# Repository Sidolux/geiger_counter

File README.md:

# geiger_counter
Geiger Counter (STS-5) designed with KiCad

PCB_SCH - KiCad project

source - uC firmware (in future)

Some changes

GPG

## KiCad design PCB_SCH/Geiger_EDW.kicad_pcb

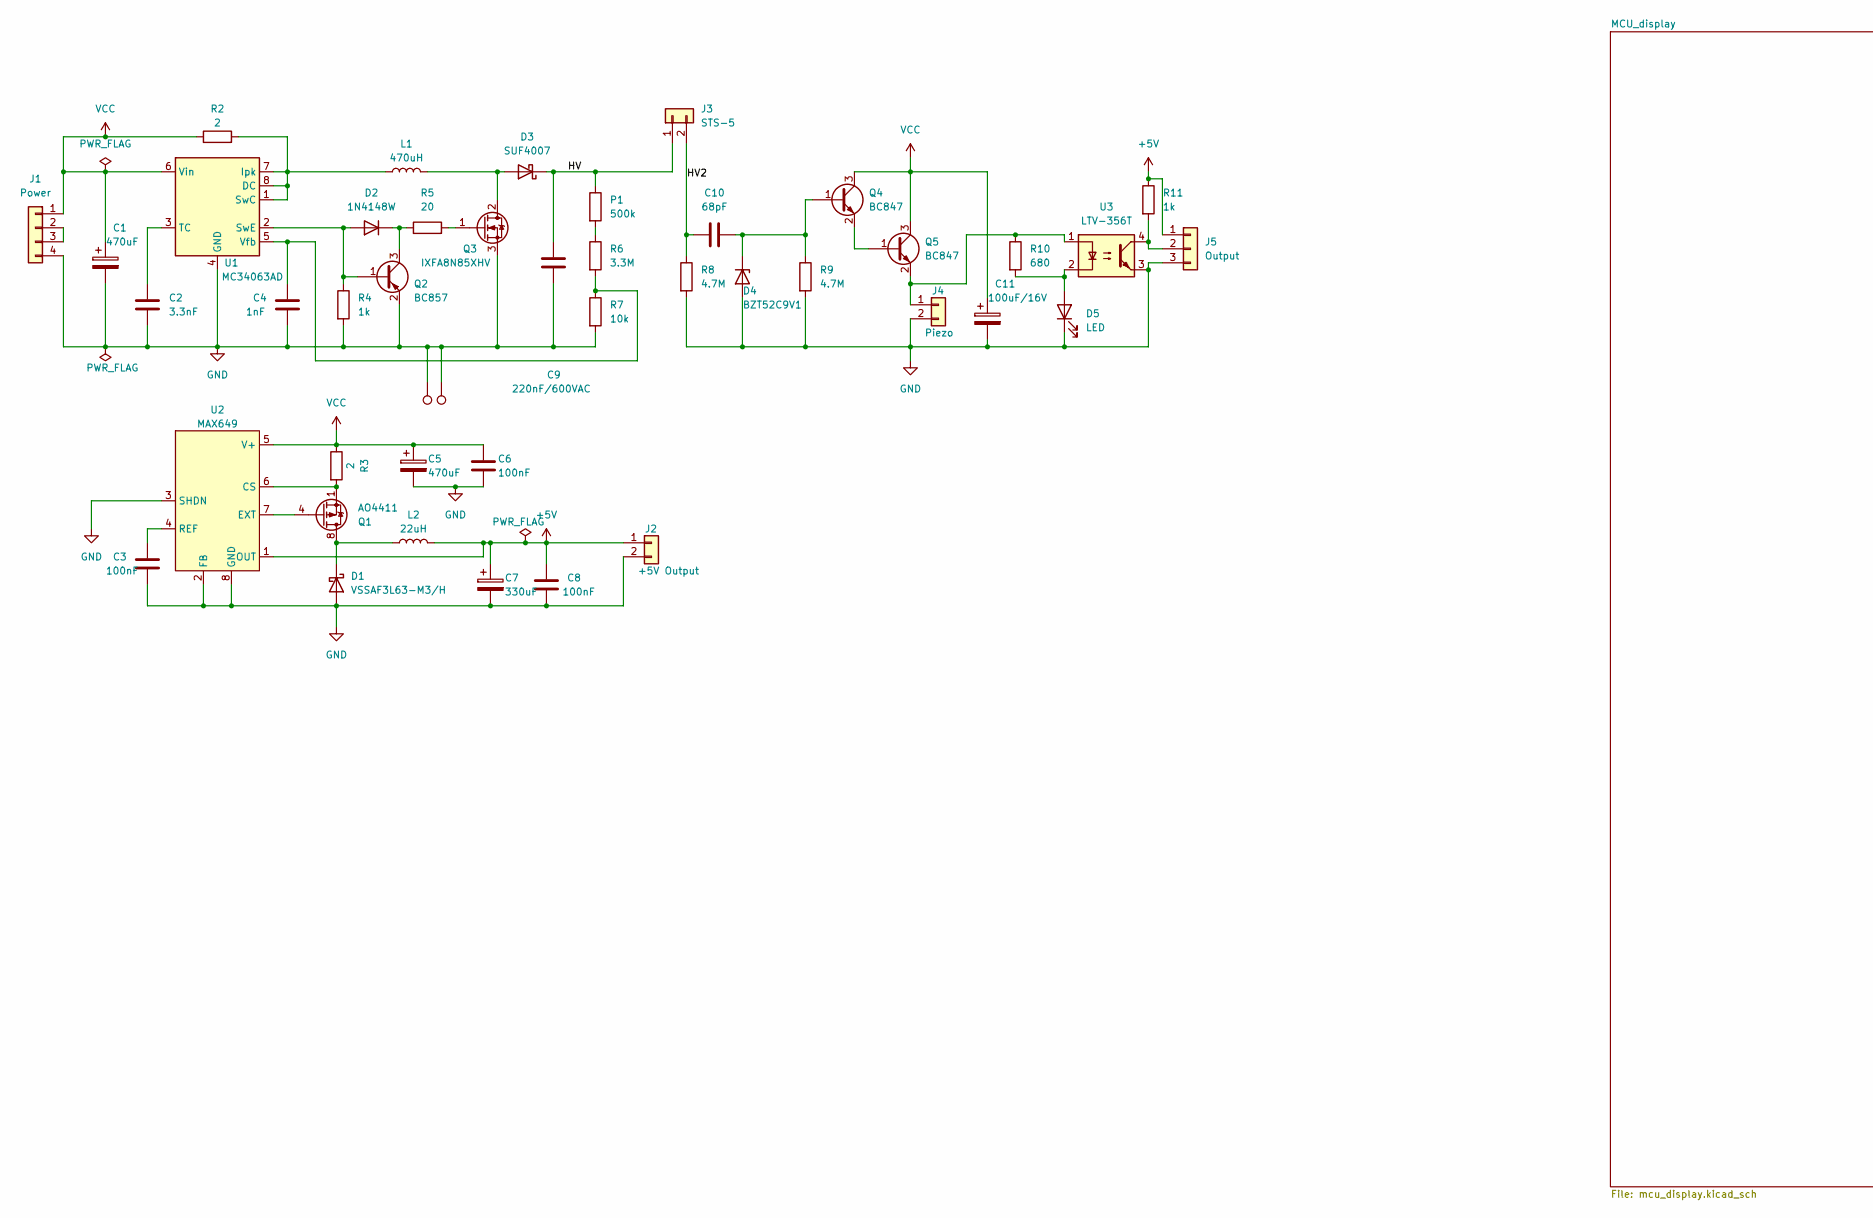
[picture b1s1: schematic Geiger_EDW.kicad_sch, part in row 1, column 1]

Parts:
C1, C5: 470uF; CP_Elec_8x10.5
C2: 3.3nF; C_1206_3216Metric_Pad1.33x1.80mm_HandSolder
C3, C6, C8: 100nF; C_1206_3216Metric_Pad1.33x1.80mm_HandSolder
C4: 1nF; C_1206_3216Metric_Pad1.33x1.80mm_HandSolder
C7: 330uF; CP_Elec_8x10.5
C9: 220nF/600VAC; C_Rect_L41.5mm_W19.0mm_P37.50mm_MKS4
C10: 68pF; C_1206_3216Metric_Pad1.33x1.80mm_HandSolder
C11: 100uF/16V; CP_Elec_8x10.5
D1: VSSAF3L63-M3/H; D_MELF
D2: 1N4148W; D_SOD-123
D3: SUF4007; D_MELF
D4: BZT52C9V1; D_SOD-123
D5: LED; LED_1206_3216Metric_Pad1.42x1.75mm_HandSolder
J1: Power; PinHeader_1x04_P2.54mm_Vertical
J2: +5V Output; PinHeader_1x02_P2.54mm_Vertical
J3: STS-5
J4: Piezo; PinHeader_1x02_P2.54mm_Vertical
J5: Output; PinHeader_1x03_P2.54mm_Vertical
L1: 470uH; L_10.4x10.4_H4.8
L2: 22uH; L_12x12mm_H6mm
P1: 500k; R_1206_3216Metric_Pad1.30x1.75mm_HandSolder
Q1: AO4411; SOIC-8_3.9x4.9mm_P1.27mm
Q2: BC857; SOT-23
Q3: IXFA8N85XHV; TO-263-2
Q4, Q5: BC847; SOT-23
R2, R3: 2; R_1206_3216Metric_Pad1.30x1.75mm_HandSolder
R4, R11: 1k; R_1206_3216Metric_Pad1.30x1.75mm_HandSolder
R5: 20; R_1206_3216Metric_Pad1.30x1.75mm_HandSolder
R6: 3.3M; R_1206_3216Metric_Pad1.30x1.75mm_HandSolder
R7: 10k; R_1206_3216Metric_Pad1.30x1.75mm_HandSolder
R8, R9: 4.7M; R_1206_3216Metric_Pad1.30x1.75mm_HandSolder
R10: 680; R_1206_3216Metric_Pad1.30x1.75mm_HandSolder
TP1, TP2: TestPoint; TestPoint_Loop_D2.60mm_Drill1.4mm_Beaded
U1: MC34063AD; SOIC-8_3.9x4.9mm_P1.27mm
U2: MAX649; SO-8_3.9x4.9mm_P1.27mm
U3: LTV-356T; SO-4_4.4x3.6mm_P2.54mm

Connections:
+5V: C7.1, C8.2, J2.1, J5.1, L2.2, R11.1, U2.1 (OUT); also elsewhere on the board
/HV: C9.1, D3.1 (K), J3.1, P1.1
/HV2: C10.2, J3.2, R8.1
GND: C1.2, C2.2, C3.2, C4.2, C5.2, C6.2, C7.2, C8.1, C9.2, C11.2, D1.2 (A), D4.2 (A), D5.1 (K), J1.4, J2.2, J4.2, J5.3, Q2.2 (E), Q3.3 (S), R4.2, R7.2, R8.2, R9.2, TP1.1, TP2.1, U1.4 (GND), U2.2 (FB), U2.3 (SHDN), U2.8 (GND), U3.3; also elsewhere on the board
unnamed: D1.1 (K), L2.1, Q1.5 (D), Q1.6 (D), Q1.7 (D), Q1.8 (D)
unnamed: D2.2 (A), Q2.1 (B), R4.1, U1.2 (SwE)
unnamed: D2.1 (K), Q2.3 (C), R5.1
unnamed: D3.2 (A), L1.2, Q3.2 (D)
unnamed: C10.1, D4.1 (K), Q4.1 (B), R9.1
unnamed: D5.2 (A), R10.2, U3.2
unnamed: J1.2, J1.3
unnamed: J4.1, Q5.2 (E), R10.1, U3.1
unnamed: J5.2, R11.2, U3.4
unnamed: P1.2, R6.1
unnamed: Q1.4 (G), U2.7 (EXT)
unnamed: Q3.1 (G), R5.2
unnamed: Q4.2 (E), Q5.1 (B)
unnamed: L1.1, R2.2, U1.1 (SwC), U1.7 (Ipk), U1.8 (DC)
unnamed: C2.1, U1.3 (TC)
unnamed: C4.1, R6.2, R7.1, U1.5 (Vfb)
unnamed: Q1.1 (S), Q1.2 (S), Q1.3 (S), R3.2, U2.6 (CS)
unnamed: C3.1, U2.4 (REF)
VCC: C1.1, C5.1, C6.1, C11.1, J1.1, Q4.3 (C), Q5.3 (C), R2.1, R3.1, U1.6 (Vin), U2.5 (V+)

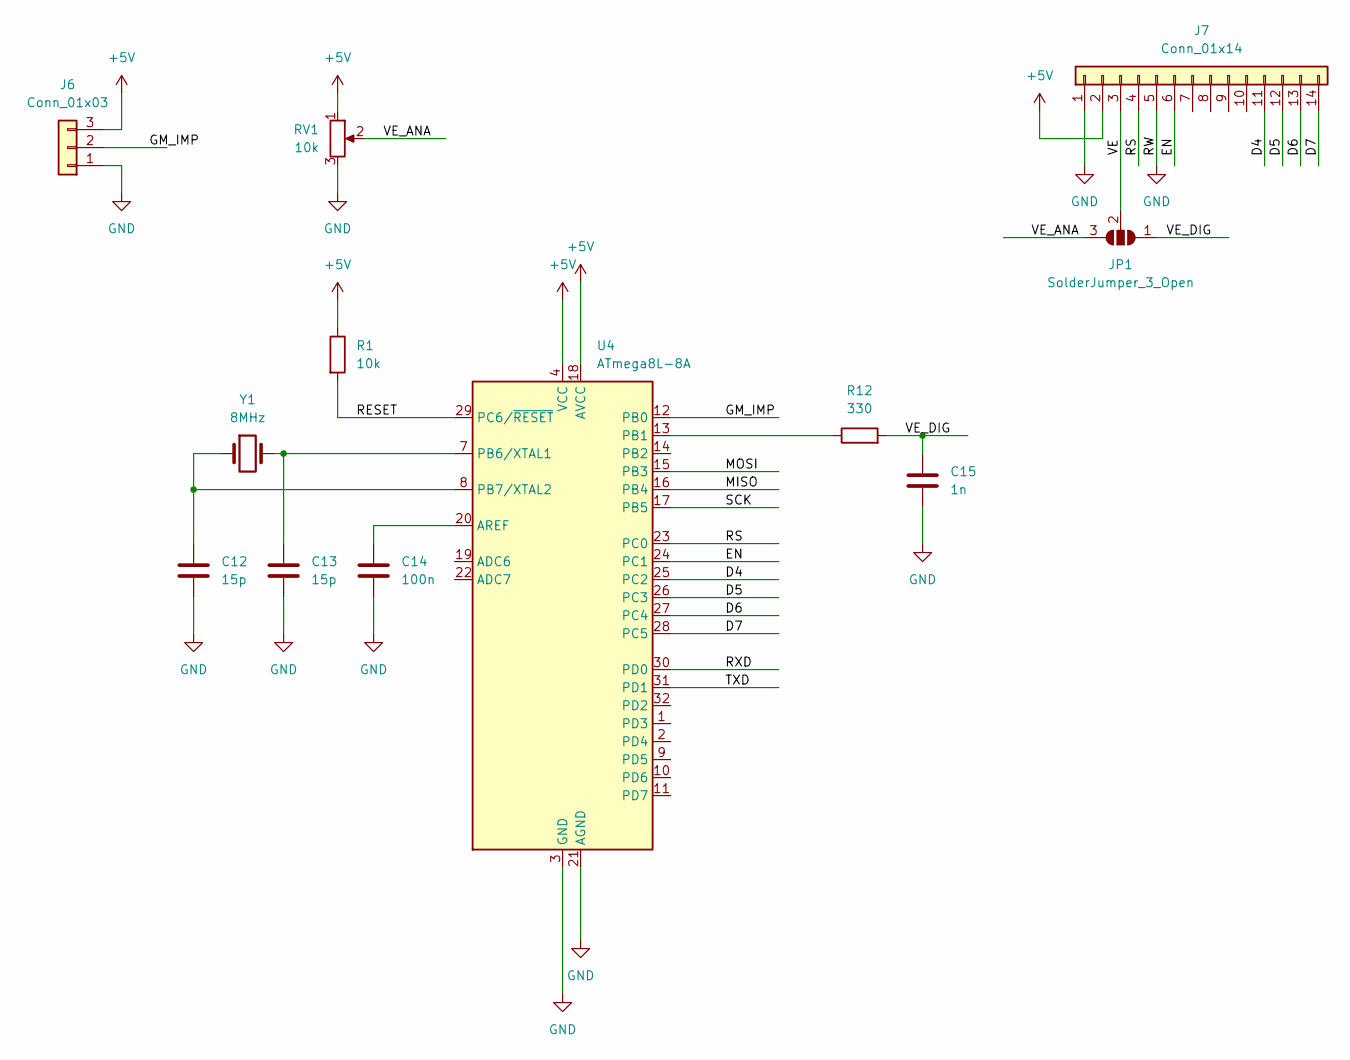
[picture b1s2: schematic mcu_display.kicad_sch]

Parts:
C12, C13: 15p; C_Disc_D3.0mm_W1.6mm_P2.50mm
C14: 100n; C_Disc_D3.8mm_W2.6mm_P2.50mm
C15: 1n; C_Disc_D3.8mm_W2.6mm_P2.50mm
J6: Conn_01x03; PinHeader_1x03_P2.54mm_Vertical
J7: Conn_01x14; PinHeader_1x14_P2.54mm_Vertical
JP1: SolderJumper_3_Open; SolderJumper-3_P2.0mm_Open_TrianglePad1.0x1.5mm_NumberLabels
R1: 10k; R_1206_3216Metric_Pad1.30x1.75mm_HandSolder
R12: 330; R_1206_3216Metric_Pad1.30x1.75mm_HandSolder
RV1: 10k; Potentiometer_ACP_CA6-H2,5_Horizontal
U4: ATmega8L-8A; TQFP-32_7x7mm_P0.8mm
Y1: 8MHz; Crystal_HC18-U_Vertical

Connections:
+5V: J6.3, J7.2, R1.1, RV1.1, U4.4 (VCC), U4.6 (VCC), U4.18 (AVCC); also elsewhere on the board
/MCU_display/D4: J7.11, U4.25 (PC2)
/MCU_display/D5: J7.12, U4.26 (PC3)
/MCU_display/D6: J7.13, U4.27 (PC4)
/MCU_display/D7: J7.14, U4.28 (PC5)
/MCU_display/EN: J7.6, U4.24 (PC1)
/MCU_display/GM_IMP: J6.2, U4.12 (PB0)
/MCU_display/MISO: U4.16 (PB4)
/MCU_display/MOSI: U4.15 (PB3)
/MCU_display/RESET: R1.2, U4.29 (PC6/~RESET)
/MCU_display/RS: J7.4, U4.23 (PC0)
/MCU_display/RXD: U4.30 (PD0)
/MCU_display/SCK: U4.17 (PB5)
/MCU_display/TXD: U4.31 (PD1)
/MCU_display/VE: J7.3, JP1.2 (C)
/MCU_display/VE_ANA: JP1.3 (B), RV1.2
/MCU_display/VE_DIG: C15.1, JP1.1 (A), R12.2
GND: C12.2, C13.2, C14.2, C15.2, J6.1, J7.1, J7.5, RV1.3, U4.3 (GND), U4.5 (GND), U4.21 (AGND); also elsewhere on the board
unnamed: C14.1, U4.20 (AREF)
unnamed: R12.1, U4.13 (PB1)
unnamed: C13.1, U4.7 (PB6/XTAL1), Y1.2
unnamed: C12.1, U4.8 (PB7/XTAL2), Y1.1

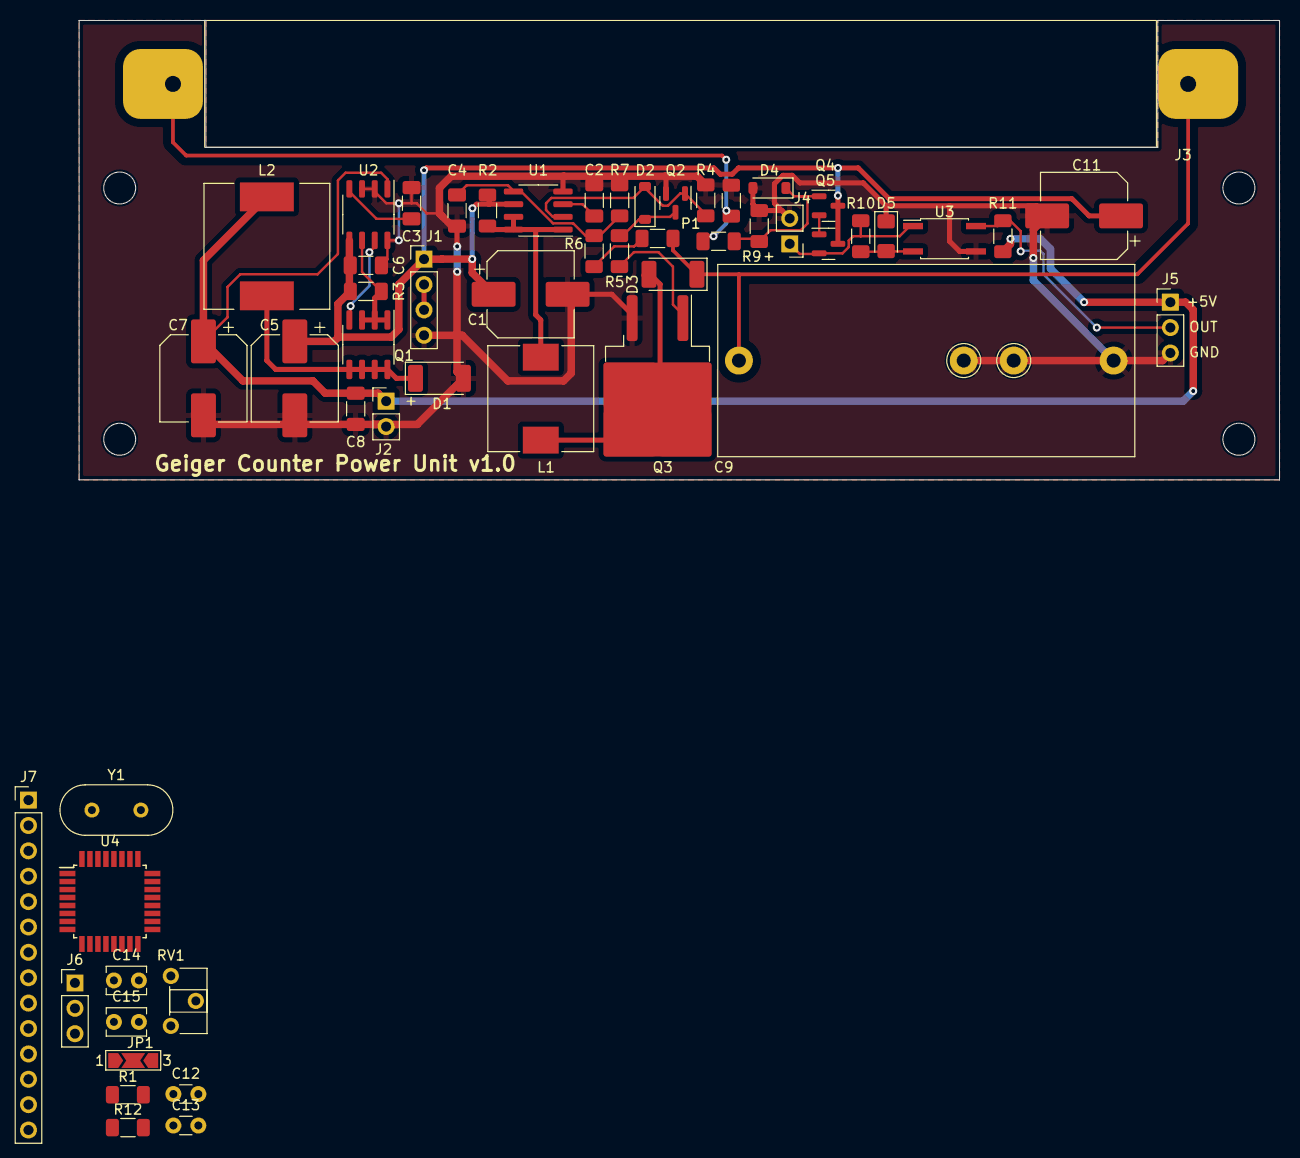
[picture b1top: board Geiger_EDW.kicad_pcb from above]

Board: 2 copper layers, 120.1 x 46.0 mm, 56 parts (0 on the bottom side), 38 nets.

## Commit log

2023-09-27 Create main code file
2023-09-27 Change R11 value from 10k to 1k
2023-09-27 Do not track backup files
2023-09-27 Create folder for KiCad project
2023-09-27 Update PCB values
2023-09-30 .gitignore
2023-09-30 New sheet, mcu added
2023-10-01 added jumper enabling selection between analog and digital contrast adjustment
2023-10-07 Update fp-info-cache
2023-10-07 Make STS holes larger (1,6mm)
2023-10-07 testpoints
2023-10-07 Cosmetics sch
2023-10-07 Update R2 value
2023-10-07 R2 change
2023-10-07 Revert "Update R2 value"
2023-10-07 Update R2 to 1ohm
2023-10-07 another r2 change
2023-10-09 Update components
2023-10-09 thumbnail
2023-10-21 README.md mods
2023-10-31 test gpg
2023-10-31 gpg recheck
2023-10-31 gpg recheck 2
2023-10-31 revert dumb test
2024-04-24 KiCad 8 format
2024-04-29 Testing Sourcetree
2024-04-29 Revert "Testing Sourcetree"
    This reverts commit 3f839b514c7613525d6594b947f07a4a2d080e29.
